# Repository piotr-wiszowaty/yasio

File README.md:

YASIO
=====

Yet another [Atari XL/XE](http://en.wikipedia.org/wiki/Atari_8-bit_family) SIO
floppy drive emulator - Yet-Another-SIO.

Features
--------

* Handles ATR and Atari executable files.
* Files stored on a micro-SD FAT32-formatted card.
* Works at speeds up to 115200 BPS.
* Controlled via a WWW browser via WiFi connection.
* Works in WiFi access point or station mode.

Hardware
--------

* Based on an ESP32-S3 devboard.
* Fits into a USB3 device enclosure.

Programming & Asembly
---------------------

Prerequisities:

* [xasm](https://github.com/pfusik/xasm)
* [foco65](https://github.com/piotr-wiszowaty/foco65)
* [PlatformIO](https://platformio.org)

0. Solder all of the components to the PCB.
1. Compile bootloader (optional): `bootloader/generate-bootloader.sh`.
2. Compile setup program: `setup/build.sh`.
3. Connect the device via USB-C cable to a PC (do not connect it to an Atari
   computer yet).
4. Flash the firmware by executing `pio run -e 0 -t upload` in `uc`
   subdirectory.
5. Disconnect the device from Atari computer; put the device in the enclosure.
   Three cutouts in the enclosure are required - for the USB socket, for the
   setup button and for the SIO cable. Note that the enclosure already has a
   hole allowing insertion/ejection of the SD card.

Usage
-----

### SD card preparation

Before turning on the device prepare an SD card - write configuration file
(`setup/yasio.conf`) and setup program (`setup/yasio_setup.xex`) to the root
directory of the SD card filesystem.

The configuration file contents may be prepared beforehand by using a text
editor or setup using the setup program. The setup program is 'inserted' into
`D1` drive by holding the setup button when turning on the device or by
pressing the setup button when the device is working and rebooting the Atari
computer.

### Configuration

Configuration file `yasio.conf` is an ASCII text file with LF-terminated lines.
Each line consists one configuration entry. Each entry starts with an entry key
followed by `:` character and (optional) entry value.
Available configuration entries and :

* `D1`, `D2`, `D3`, `D4` - path to file 'inserted' into appropriate drive;
  e.g.: `D1:demo/Drunk Chessboard.atr`
* `MO` - work mode; available values: `Station`, `AccessPoint`
* `AP` - WiFi access point parameters: SSID, password, IP-address/netmask;
  e.g.: `AP:My_ssid my_password 192.168.8.1/24`
* `ST` - WiFi station parameters: SSID, password; e.g.: `Some_ssid
  password123`; may occur multiple times

### WiFi

In access point mode the device advertises itself using the configured SSID and
password. The device address assigned is also taken from the configuration.

In station mode the configured access points are tried in the given order until
a connection to one succeeds. The assigned address may be retrieved by running
the setup program (pressing spacebar may be necessary to refresh the address
shown).

### LED indicator colors

* green - SD card initialization successful, WiFi initialization successful
* red - SD card initialization failure
* purple - failure connecting to WiFi access point

References
----------

The bootloader used for loading executable files is based on one
found in [Atari800](https://atari800.github.io/).

The code for controlling the LED on the devboard is by Espressif Systems
(Shanghai) CO LTD.

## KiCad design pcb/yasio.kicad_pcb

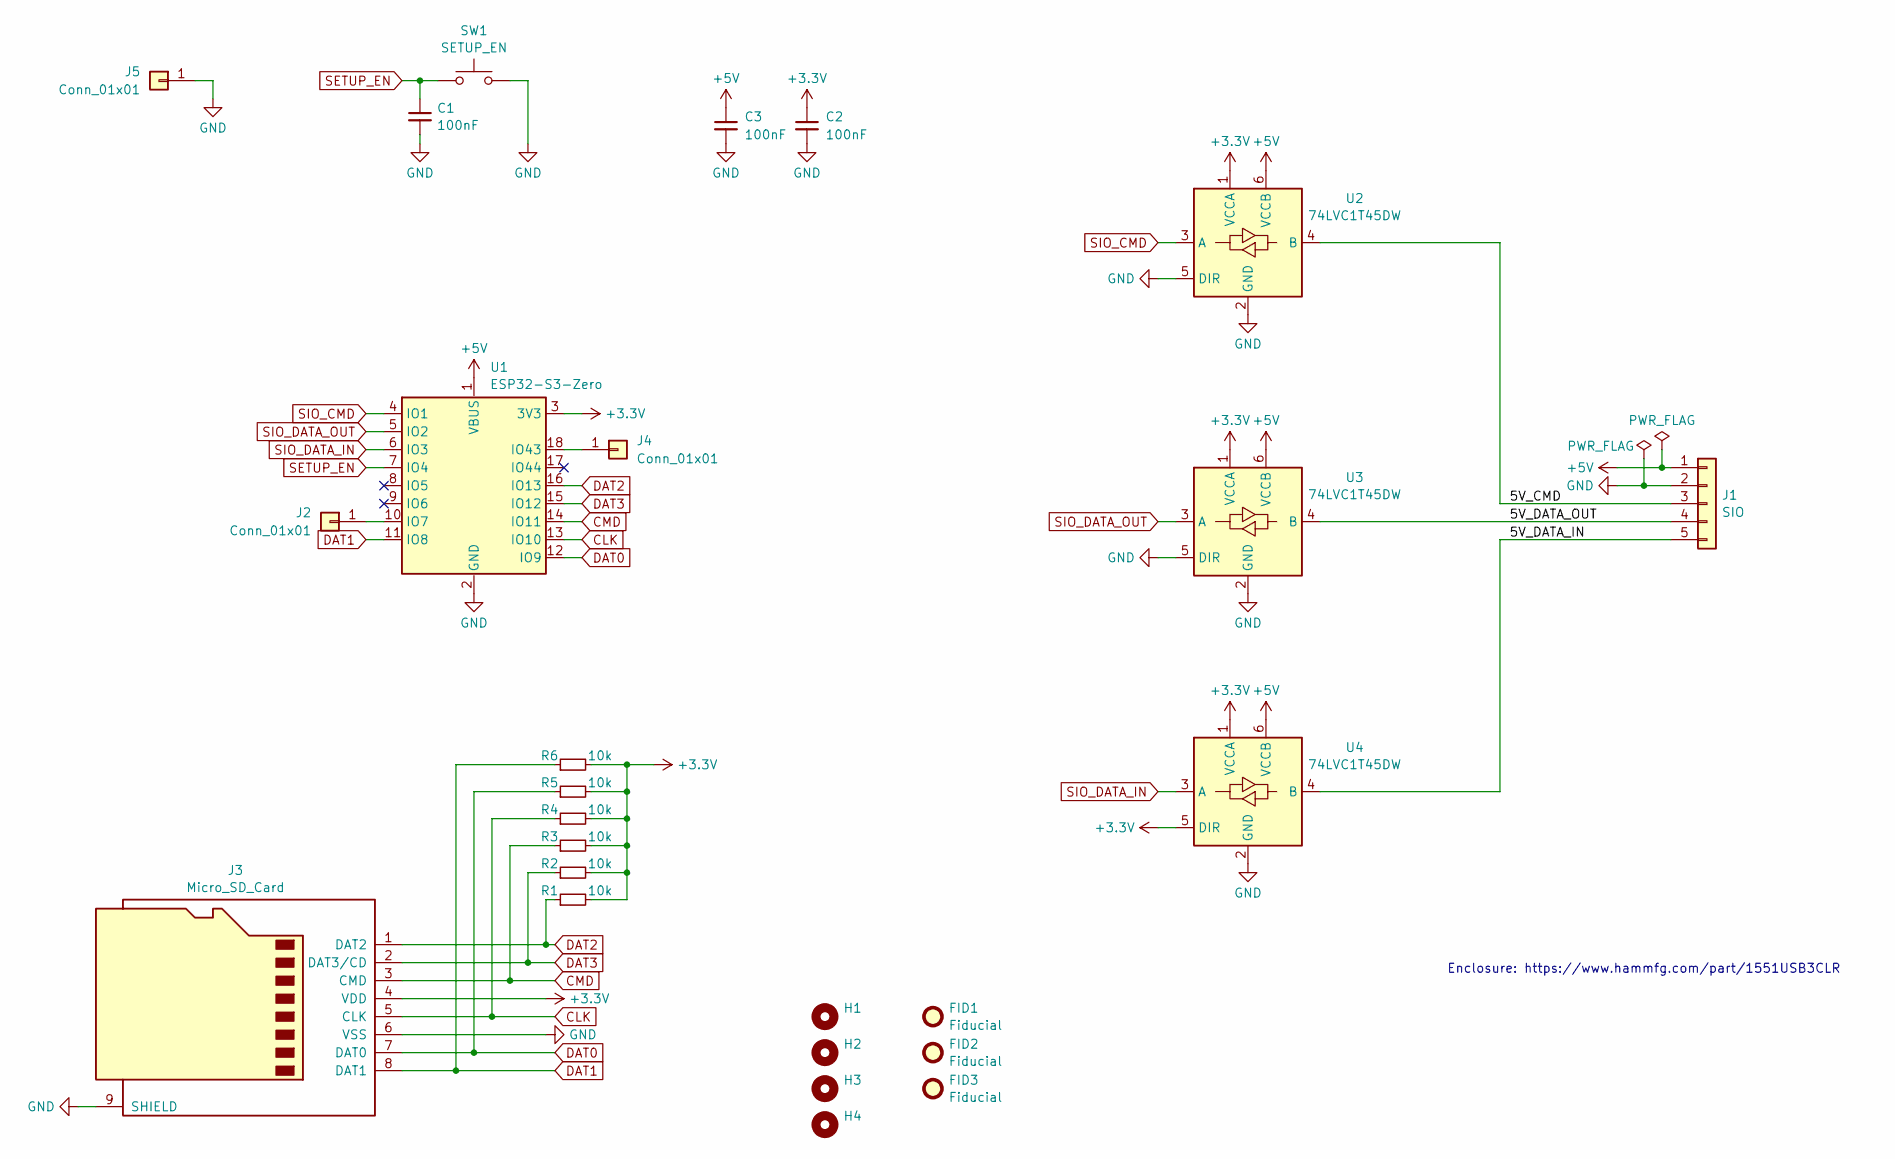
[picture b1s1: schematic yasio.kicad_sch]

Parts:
C1, C2, C3: 100nF; C_0805_2012Metric_Pad1.18x1.45mm_HandSolder
FID1, FID2, FID3: Fiducial; Fiducial_0.75mm_Mask1.5mm
H1, H2, H3, H4: MountingHole; MountingHole_2.2mm_M2
J1: SIO; PinHeader_1x05_P2.54mm_Vertical
J2, J4, J5: Conn_01x01; PinHeader_1x01_P2.54mm_Vertical
J3: Micro_SD_Card; microSD_HC_Hirose_DM3BT-DSF-PEJS
R1, R2, R3, R4, R5, R6: 10k; R_0805_2012Metric_Pad1.20x1.40mm_HandSolder
SW1: SETUP_EN; SW_Push_1P1T_NO_CK_KSC9xxGxxx
U1: ESP32-S3-Zero
U2, U3, U4: 74LVC1T45DW; SOT-363_SC-70-6_Handsoldering

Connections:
+3.3V: C2.1, J3.4 (VDD), R1.2, R2.2, R3.2, R4.2, R5.2, R6.2, U1.3 (3V3), U2.1 (VCCA), U3.1 (VCCA), U4.1 (VCCA), U4.5 (DIR)
+5V: C3.1, J1.1, U1.1 (VBUS), U2.6 (VCCB), U3.6 (VCCB), U4.6 (VCCB)
/5V_CMD: J1.3, U2.4 (B)
/5V_DATA_IN: J1.5, U4.4 (B)
/5V_DATA_OUT: J1.4, U3.4 (B)
CLK: J3.5 (CLK), R4.1, U1.13 (IO10)
CMD: J3.3 (CMD), R3.1, U1.14 (IO11)
DAT0: J3.7 (DAT0), R5.1, U1.12 (IO9)
DAT1: J3.8 (DAT1), R6.1, U1.11 (IO8)
DAT2: J3.1 (DAT2), R1.1, U1.16 (IO13)
DAT3: J3.2 (DAT3/CD), R2.1, U1.15 (IO12)
GND: C1.2, C2.2, C3.2, J1.2, J3.6 (VSS), J3.9 (SHIELD), J5.1, SW1.2, U1.2 (GND), U2.2 (GND), U2.5 (DIR), U3.2 (GND), U3.5 (DIR), U4.2 (GND)
unnamed: J2.1, U1.10 (IO7)
unnamed: J4.1, U1.18 (IO43)
SETUP_EN: C1.1, SW1.1, U1.7 (IO4)
SIO_CMD: U1.4 (IO1), U2.3 (A)
SIO_DATA_IN: U1.6 (IO3), U4.3 (A)
SIO_DATA_OUT: U1.5 (IO2), U3.3 (A)

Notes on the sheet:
Enclosure: https://www.hammfg.com/part/1551USB3CLR

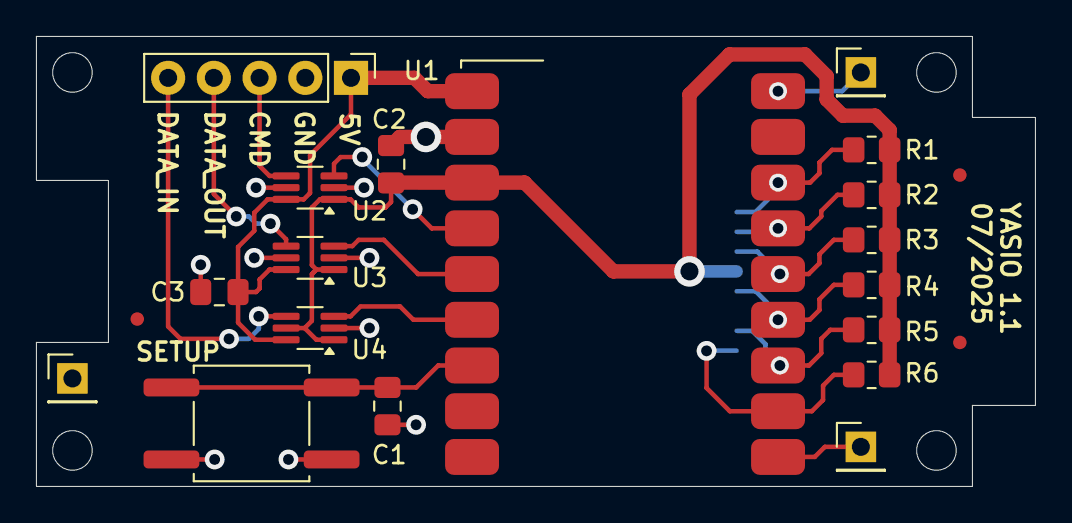
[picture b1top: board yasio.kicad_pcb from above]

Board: 2 copper layers, 55.5 x 25.0 mm, 26 parts (1 on the bottom side), 18 nets.

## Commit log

2025-07-19 Add executable files bootloader
2025-07-19 Add icons
2025-07-19 Add microcontroller firmware source code
2025-07-19 Add PCB design files
2025-07-19 Add setup program source code
2025-07-19 Add PCB CAM files
2025-07-20 Update setup build script
2025-07-20 Add entries to example config file
